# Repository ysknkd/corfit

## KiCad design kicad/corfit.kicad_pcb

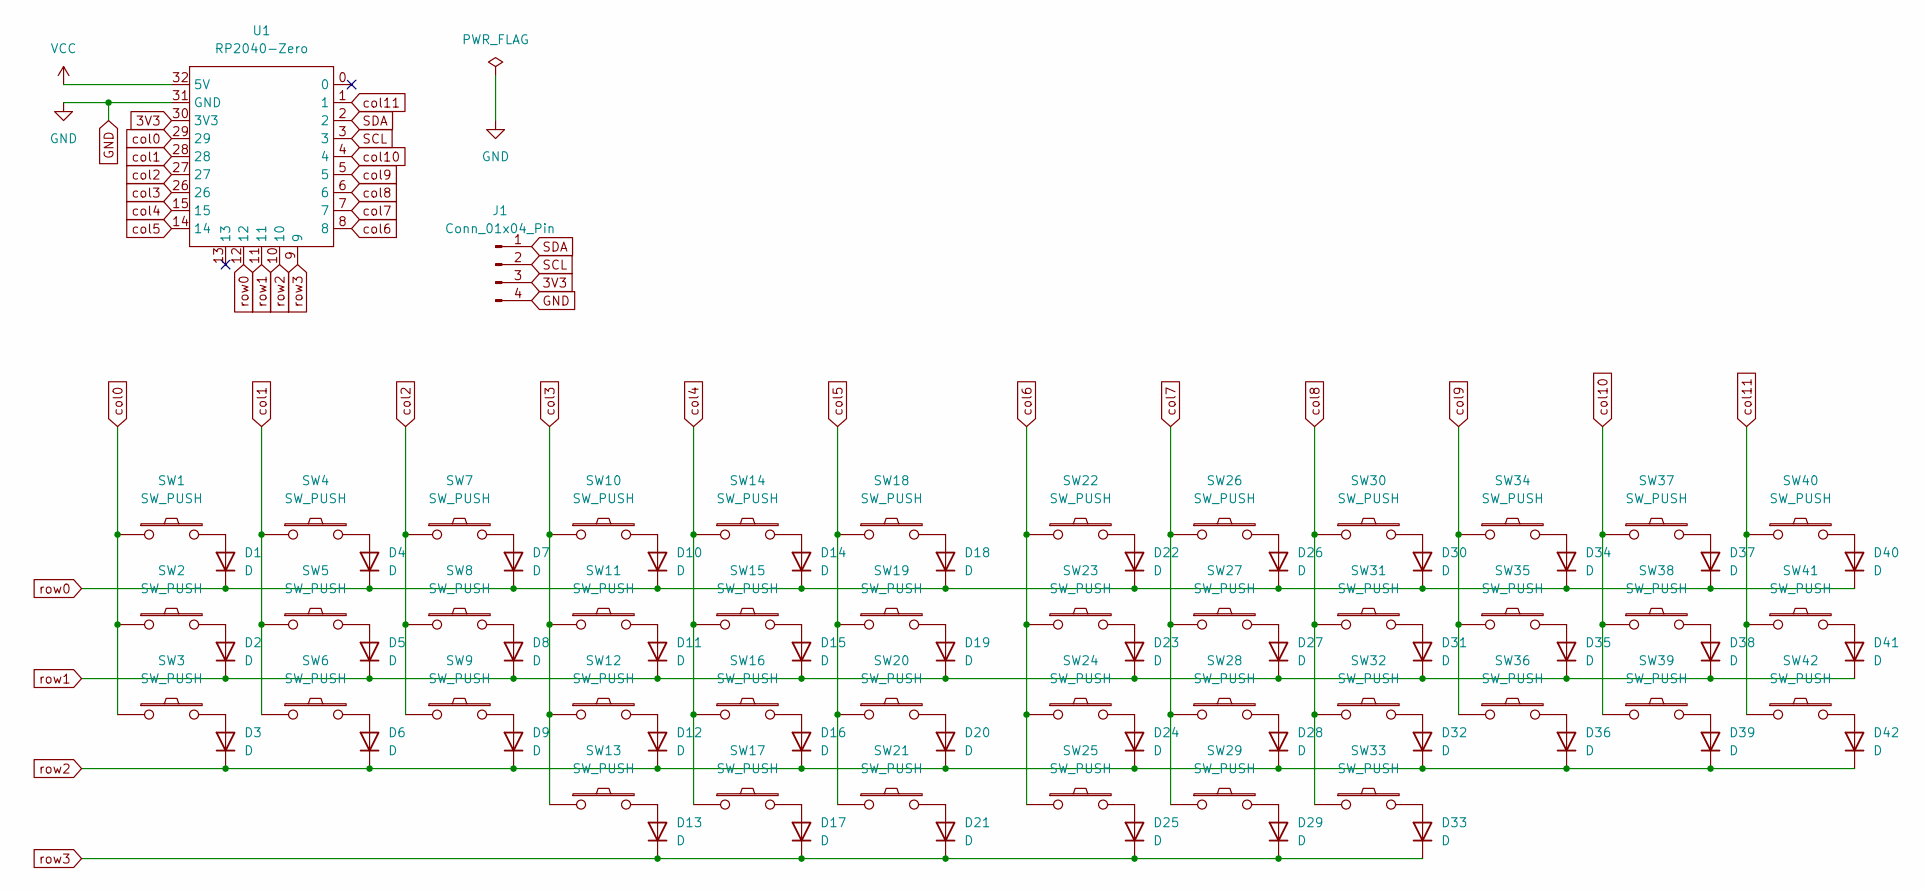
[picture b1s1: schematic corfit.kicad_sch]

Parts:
D1, D2, D3, D4, D5, D6, D7, D8, D9, D10, D11, D12, D13, D14, D15, D16, D17, D18, D19, D20, D21, D22, D23, D24, D25, D26, D27, D28, D29, D30, D31, D32, D33, D34, D35, D36, D37, D38, D39, D40, D41, D42: D; Diode_SMD
J1: Conn_01x04_Pin; TPS43_Cutout_Middle
SW1, SW2, SW3, SW4, SW5, SW6, SW7, SW8, SW9, SW10, SW11, SW12, SW13, SW14, SW15, SW16, SW17, SW18, SW19, SW20, SW21, SW22, SW23, SW24, SW25, SW26, SW27, SW28, SW29, SW30, SW31, SW32, SW33, SW34, SW35, SW36, SW37, SW38, SW39, SW40, SW41, SW42: SW_PUSH; Choc_Hotswap_1u
U1: RP2040-Zero

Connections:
3V3: J1.3, U1.30 (3V3)
GND: J1.4, U1.31 (GND)
unnamed: D1.2 (A), SW1.2
unnamed: D2.2 (A), SW2.2
unnamed: D3.2 (A), SW3.2
unnamed: D4.2 (A), SW4.2
unnamed: D5.2 (A), SW5.2
unnamed: D6.2 (A), SW6.2
unnamed: D7.2 (A), SW7.2
unnamed: D8.2 (A), SW8.2
unnamed: D9.2 (A), SW9.2
unnamed: D10.2 (A), SW10.2
unnamed: D11.2 (A), SW11.2
unnamed: D12.2 (A), SW12.2
unnamed: D13.2 (A), SW13.2
unnamed: D14.2 (A), SW14.2
unnamed: D15.2 (A), SW15.2
unnamed: D16.2 (A), SW16.2
unnamed: D17.2 (A), SW17.2
unnamed: D18.2 (A), SW18.2
unnamed: D19.2 (A), SW19.2
unnamed: D20.2 (A), SW20.2
unnamed: D21.2 (A), SW21.2
unnamed: D22.2 (A), SW22.2
unnamed: D23.2 (A), SW23.2
unnamed: D24.2 (A), SW24.2
unnamed: D25.2 (A), SW25.2
unnamed: D26.2 (A), SW26.2
unnamed: D27.2 (A), SW27.2
unnamed: D28.2 (A), SW28.2
unnamed: D29.2 (A), SW29.2
unnamed: D30.2 (A), SW30.2
unnamed: D31.2 (A), SW31.2
unnamed: D32.2 (A), SW32.2
unnamed: D33.2 (A), SW33.2
unnamed: D34.2 (A), SW34.2
unnamed: D35.2 (A), SW35.2
unnamed: D36.2 (A), SW36.2
unnamed: D37.2 (A), SW37.2
unnamed: D38.2 (A), SW38.2
unnamed: D39.2 (A), SW39.2
unnamed: D40.2 (A), SW40.2
unnamed: D41.2 (A), SW41.2
unnamed: D42.2 (A), SW42.2
SCL: J1.2, U1.3
SDA: J1.1, U1.2
VCC: U1.32 (5V)
col0: SW1.1, SW2.1, SW3.1, U1.29
col1: SW4.1, SW5.1, SW6.1, U1.28
col2: SW7.1, SW8.1, SW9.1, U1.27
col3: SW10.1, SW11.1, SW12.1, SW13.1, U1.26
col4: SW14.1, SW15.1, SW16.1, SW17.1, U1.15
col5: SW18.1, SW19.1, SW20.1, SW21.1, U1.14
col6: SW22.1, SW23.1, SW24.1, SW25.1, U1.8
col7: SW26.1, SW27.1, SW28.1, SW29.1, U1.7
col8: SW30.1, SW31.1, SW32.1, SW33.1, U1.6
col9: SW34.1, SW35.1, SW36.1, U1.5
col10: SW37.1, SW38.1, SW39.1, U1.4
col11: SW40.1, SW41.1, SW42.1, U1.1
row0: D1.1 (K), D4.1 (K), D7.1 (K), D10.1 (K), D14.1 (K), D18.1 (K), D22.1 (K), D26.1 (K), D30.1 (K), D34.1 (K), D37.1 (K), D40.1 (K), U1.12
row1: D2.1 (K), D5.1 (K), D8.1 (K), D11.1 (K), D15.1 (K), D19.1 (K), D23.1 (K), D27.1 (K), D31.1 (K), D35.1 (K), D38.1 (K), D41.1 (K), U1.11
row2: D3.1 (K), D6.1 (K), D9.1 (K), D12.1 (K), D16.1 (K), D20.1 (K), D24.1 (K), D28.1 (K), D32.1 (K), D36.1 (K), D39.1 (K), D42.1 (K), U1.10
row3: D13.1 (K), D17.1 (K), D21.1 (K), D25.1 (K), D29.1 (K), D33.1 (K), U1.9

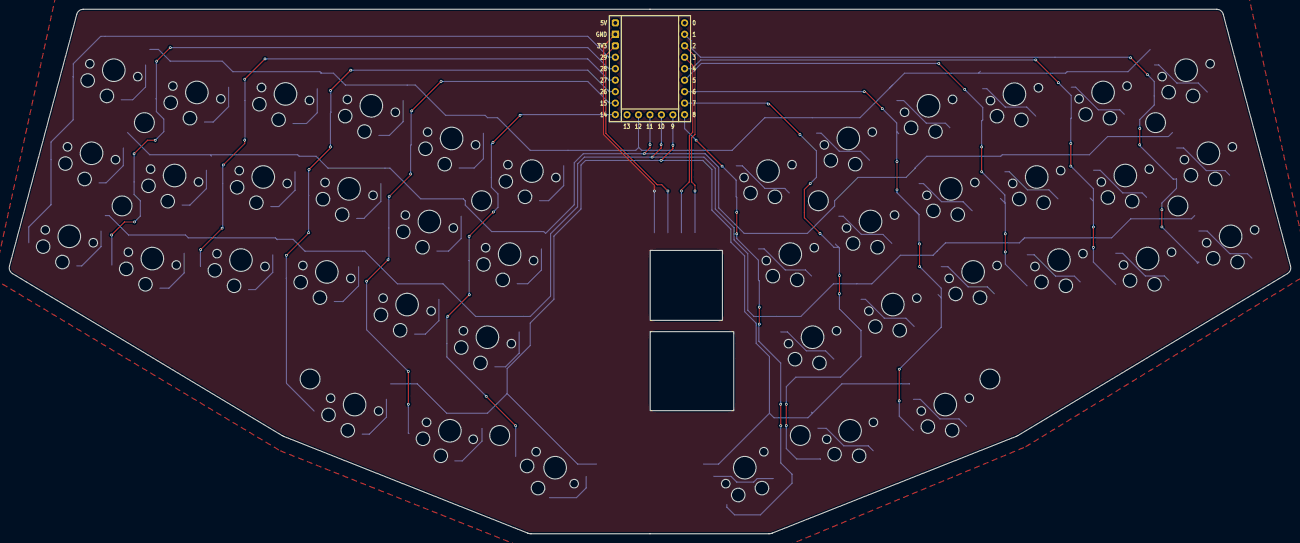
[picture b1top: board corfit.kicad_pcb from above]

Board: 2 copper layers, 283.9 x 116.2 mm, 96 parts (0 on the bottom side), 62 nets.

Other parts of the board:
Ref**: M2_SpacerHole
Ref**#2, Ref**#3, Ref**#4, Ref**#5, Ref**#6, Ref**#7, Ref**#8, Ref**#9, Ref**#10: M2_SpacerHole
